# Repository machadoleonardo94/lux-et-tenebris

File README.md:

# Lux et Tenebris

**Lux et Tenebris** is an open-source ESP32-based LED controller development platform featuring custom PCB hardware, firmware, and support for addressable LEDs, RGB strips, and various lighting effects.

## Disclaimer

### Most of the readme.md present here was writen by Clanker, as a proof of concept for fast doccumentation generation. It may not contain the newest features, but it's good enough as a placeholder. Considering that it took 2 prompts and minor fixes, time that would've been used on this document was allocated elsewere more productive, like the main features.

But you know what? Using Clankers' template made the doccumentation much more enjoyable, and ended up with way more content than all of my previous projects combined, as after reading it I've managed to add tidbits that I wouldn't have written otherwise.

## Demo Video

https://github.com/user-attachments/assets/9bc4d82b-29f8-49ef-8373-876afc4fa7dd

### [Install firmware](install/)
A fresh, blank board needs nothing but a browser. Open the flasher in **Chrome or Edge on a
desktop**, plug the ESP32-C3 in over USB-C, click **Install** — no Python, no esptool, no USB-serial
driver, because the C3's USB is native.

**[⚡ Browser installer](install/)** · **[⬇ Release downloads](Firmware/lightpack-C3/releases/)** · **[How the installer works](install/README.md)**

- It explains itself when it cannot work (Firefox, Safari, mobile, or a `file://` copy) instead of
  showing a dead button, and links the command-line fallback.
- Works offline as well: serve this repository with `python -m http.server 8000` and open
  <http://localhost:8000/install/>.
- After flashing: join the `Lightpack-Devkit` hotspot, then use <http://lightpack.local>.

### [Hardware](Hardware/)
Custom PCB designs created in KiCad for the Lux et Tenebris devkit. Includes production-ready files for JLCPCB assembly.

**[📖 Hardware Documentation](Hardware/README.md)**

**Features:**
- ESP32-based design (4MB Flash)
- USB-C connectivity
- 4x WS2812B addressable LED channels
- 3x Open drain outputs + 1x controlled current output
- I2C expansion port for OLED display (SSD1306)
- Multiple expansion ports (Serial, I2C, GPIO)
- Production files ready for manufacturing

### [Firmware](Firmware/)
Arduino-based firmware with WiFi connectivity, OTA updates, and dynamic LED effects. Two
boards, two projects:

| Project | Board | Status | Install |
|---|---|---|---|
| **[lightpack-C3](Firmware/lightpack-C3/)** | Lux et Portabilis **V2** (ESP32-C3 SuperMini) | **Pre-release V0.4-pre** | **[⚡ Browser installer](install/)** · **[⬇ Downloads](Firmware/lightpack-C3/releases/V0.4-pre/)** |
| [lightpack](Firmware/lightpack/) | Lux et Tenebris **Devkit** (ESP32-WROOM) | V1.0 | Build from source |

**lightpack-C3 (Portabilis V2)** — current work:

- WiFi connectivity with captive portal configuration, 2 saved networks, offline (radio-off) mode
- Two OTA paths: ArduinoOTA and a **browser firmware upload** from the device page
- Single-channel WS2812B LED control with 5 modes (solid, flame, gyro fade, pulse whip, rainbow)
- MPU6050 accelerometer, impact detector, I²C bus scan, rail-voltage telemetry
- Battery latch power control, on-device menu, non-volatile storage for every setting
- 5 versioned preset slots with web import/export
- **[⚡ Browser installer](install/)**: Flash a blank board from Chrome/Edge — no tools, no drivers
- **[📖 Firmware Documentation](Firmware/lightpack-C3/README.md)** · **[📋 Release notes](Firmware/lightpack-C3/CHANGELOG.md)** · **[⬇ V0.4-pre binaries](Firmware/lightpack-C3/releases/V0.4-pre/)**

**lightpack (Devkit V1)** — **[📖 Firmware Documentation](Firmware/lightpack/README.md)**

- Multi-channel WS2812B LED control with effects
- OLED display integration
- Power management and deep sleep support
- User interface with button controls

##  Key Features

### Hardware Capabilities
- **4 Independent addressable LED Channels**: Control multiple WS2812B strips simultaneously
- **High-Current Outputs**: Open drain and constant current outputs for various LED types
- **Expandable Design**: JST-GH connectors for easy expansion
- **Compact Form Factor**: Optimized between integration into props and projects, and ease to build.

### Firmware Capabilities
- **Dynamic LED Effects**: Breathing, color cycling, chase effects, and custom patterns
- **WiFi Management**: Easy network configuration via captive portal
- **OTA Updates**: Update firmware wirelessly without USB connection
- **Display Integration**: Real-time status information on OLED
- **Power Efficient**: Deep sleep mode and WiFi toggle for battery applications
- **Customizable**: Modular code structure for easy modification

##  Use Cases

- **Cosplay Props**: Control LEDs in costumes, masks, and accessories
- **Art Installations**: Multi-channel LED art with dynamic effects
- **Home Automation**: WiFi-connected lighting control
- **Prototyping**: Development platform for LED-based projects
- **Educational**: Learn ESP32, LED control, and PCB design

## 📚 Documentation

- **[Hardware Documentation](Hardware/README.md)**: PCB design, assembly, and manufacturing
- **[Browser installer](install/)**: How to flash a fresh board, and how to run/host the flasher
- **[Portabilis V2 Firmware](Firmware/lightpack-C3/README.md)**: Download, flashing, controls, web API
- **[Portabilis V2 Release notes](Firmware/lightpack-C3/CHANGELOG.md)**: What shipped, upgrade notes, known issues
- **[Firmware Documentation](Firmware/lightpack/README.md)**: Devkit V1 setup, configuration, and API reference
- **Pinout Reference**: See the per-board firmware README for complete pin assignments
- **Manufacturing Files**: BOM, positions, and Gerbers in `Hardware/*/production/`

## 🧰 Technology Stack

### Hardware
- **PCB Design**: KiCad 9.0
- **Microcontroller**: ESP32-WROOM-32
- **Manufacturing**: JLCPCB-ready production files
- **Components**: Standard 0805 SMD parts for easy sourcing

### Firmware
- **Framework**: Arduino (PlatformIO)
- **Platform**: Espressif32
- **Language**: C++
- **Libraries**: Adafruit GFX, NeoPixel, WiFiManager, ArduinoOTA

## 💡 Getting Help

- **Hardware Issues**: See [Hardware README](Hardware/README.md)
- **Firmware Issues**: See [Firmware README](Firmware/lightpack/README.md)
- **Pin Configurations**: Check `Firmware/lightpack/src/shared/pinout.h`
- **GitHub Issues**: [Report bugs or request features](https://github.com/machadoleonardo94/lux-et-tenebris/issues)

##  Acknowledgments

Special thanks to:
- The ESP32 and Arduino communities
- Espressif 
- KiCad development team
- PlatformIO for the excellent development platform
- All contributors and users of this project

---

## License

This project is released under the **BSD Zero Clause License (0BSD)** — see [`LICENSE`](LICENSE).
Use it, modify it, sell it, strip my name off it, no conditions and no attribution required.

Two things that come with that:

- **Compiled firmware images link third-party libraries** whose licenses travel with the binary. The
  Arduino-ESP32 core (LGPL-2.1-or-later) and Adafruit NeoPixel (LGPL-3.0-or-later) are the ones with
  real terms: keep their notices, keep them under LGPL, and make sure recipients can reach the source
  to relink. Everything else is MIT/BSD/Apache. Full audit, per-library copyright lines and license
  texts in [`THIRD-PARTY-NOTICES.md`](THIRD-PARTY-NOTICES.md) and [`LICENSES/`](LICENSES/).
- **The KiCad symbol libraries** used by the schematics are CC-BY-SA-4.0 with a design exception, so
  using them imposes nothing on the boards. Their files are not redistributed here.

---

**Note**: This is an active development project. Hardware and firmware specifications may change. Always refer to the specific version documentation when building or programming your device.

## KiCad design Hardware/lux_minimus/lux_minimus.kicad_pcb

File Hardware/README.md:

# Lux et Tenebris Hardware

Hardware design files for the **Lux et Tenebris Devkit** - an ESP32-based LED controller development board with integrated OLED display, WS2812B LED channels, and multiple output configurations.

## Overview

The Lux et Tenebris hardware consists of custom PCB designs created in KiCad, providing a compact platform for controlling addressable LEDs, RGB strips, and other lighting applications. The board integrates power management and some I/O expansion ports.

## Hardware Versions

### lux-et-pcb (V1.0)
- Initial release
- Core ESP32 functionality
- DC 5521 connector for 5~24V external power
- USB-C charging port
- No integrated USB-Serial converter, requires an external one for burning firmware
- Optional 1S lithium charger and battery
- 4x WS2812B LED channels (5V from regulator or internal battery)
  - GPIOs 32, 33, 19 and 16 
- 3x Open drain outputs (for 12V RGB strips)
  - GPIOs 27, 26 and 25
- 1x Controlled current output (avoid pesky short-circuits frying your wires)
  - GPIO 13
- 2x expansion port with 3V3 power
  - Those can be set as other functions for external hardware
  - GPIOs 21 and 22 for I2C devices (display, gyro, be creative)
  - GPIOs 18 and 19 expansion port (control buttons)

### lux-et-pcb-V2
- Work in progress
- Changed the processor to ESP32-S3
- Added USB-C Serial interface (no more aditional hardware required for flashing)
- Added Sound output (be funky, no idea if it will work tho)
- Added microSD slot for SDMMC
- Modular schematic organization
- To do: 
  - Add I2S support (crispy sounds)
  - Add gyro support (so the board can do a PEW PEW noise when hit)
  - Remove added latch power-on switch 

## Features

### Core Specifications
- **Microcontroller**: ESP32 (4MB Flash)
- **Power Input**: USB-C connector or 5~24V 5521 connector (good old P4 with positive inside)
- **Display**: 0.96" SSD1306 OLED (128x64, I2C)
- **LED Channels**: 4x addressable WS2812B outputs
- **Power Outputs**: 3x open drain + 1x controlled current
- **Programming**: External USB-to-Serial (CP210x or CH340) or OTA
- **Expansion Ports**: Serial, I2C, GPIOs

### Pinout

#### WS2812B LED Channels
| Channel   | GPIO Pin | Default Use              |
|-----------|----------|--------------------------|
| Channel 0 | GPIO 32  | Onboard LED ring (6 LEDs) |
| Channel 1 | GPIO 33  | External connector        |
| Channel 2 | GPIO 19  | External connector        |
| Channel 3 | GPIO 16  | External connector        |

#### Expansion Ports
| Port  | Connector | Pins                     | Function             |
|-------|-----------|--------------------------|----------------------|
| PORT1 | JST-GH 4P | GND, TX0, RX0, 5V        | Serial/Power         |
| PORT2 | JST-GH 4P | GND, GPIO18, GPIO17, 3V3 | Button/GPIO Inputs   |
| PORT3 | JST-GH 4P | GND, SCL, SDA, 3V3       | I2C Display/Sensors  |

#### Power Outputs
- **CC Output**: GPIO 13 - Constant current output (~700mA) for high-power LEDs
- **Open Drain**: GPIO 27, 26, 25 - For RGB strips or high-current switching

### Key Components
- ESP32-WROOM-32 module
- Programming and reset push buttons
- USB-C connector (GT-USB-7101A, optional)
- JST-GH 1.25mm connectors (4-pin)
- Good quality 220uF 25V 6.3x7.7mm (bad quality ones tend to heat up)
- SSD1306 0.96" OLED display (optional)
- Onboard WS2812B LED ring (optional)
- Onboard 1S lithium battery and charger (optional)
- Onboard LED for 3V3 and battery charging status (optional)
- AO340X N-MOS SOT23 transistors or equivalent that can handle at least 1A for each open collector strip channel

Full list should be on the BoM files, with codes for used component on LCSC

## PCB Design Files

Each hardware version includes:
- **`.kicad_pcb`** - PCB layout file
- **`.kicad_sch`** - Schematic file
- **`.kicad_pro`** - Project configuration
- **`.step`** - 3D model for mechanical integration
- **`production/`** - Manufacturing files (BOM, positions, netlist) for JLCPCB

## Manufacturing

### JLCPCB Assembly Service

The design is optimized for JLCPCB's PCB assembly service:

1. **PCB Fabrication + Assembly**: ~$130 for 5 boards (assembled)
2. **Files Included**:
   - `bom.csv` - Bill of Materials
   - `positions.csv` - Component placement data
   - `netlist.ipc` - Connectivity information
   - `designators.csv` - Component reference designators

### DIY Assembly

For self-assembly:
- **Cost**: $8-15 per board (components only)
- **Recommended**: Solder stencil (~$7) for SMD components, and a reflow hotbed at 250ºC for melting solder paste
- **Skills**: Intermediate soldering (fine-pitch SMD)
- **Time**: ~1-3 hours per board.  

### Component Sourcing

Most components are standard and available from:
- JLCPCB parts library (for assembly service)
- LCSC
- Mouser
- DigiKey
- Aliexpress

Special components:
- **USB-C connector**: GT-USB-7101A (included in design files)
Getting the correct USB-C connector with dozen of options is very hard if sourcing from Aliexpress.
If you do not require USB-C charging, this component can be avoided.

## Getting Started

### Prerequisites

1. **KiCad 8.0 or later** - [Download here](https://www.kicad.org/download/)
2. **3D Models** - Included `.step` files for mechanical clearance verification
3. **Symbol Library** - Custom `USB_C-8p.kicad_sym` included in project

### Generating Manufacturing Files

1. Open the PCB file in KiCad
2. Add the JLCPCB plugin from the Plugin and Content Manager
3. **Tools → External plugins → Fabrication toolkit**
4. Files should be generated on the production folder automagically 

## Assembly Instructions

### Hardware Assembly

0. **Read the issues and notes before assembly!**

1. **Solder SMD Components** (if self-assembling):
   - Use solder paste and stencil
   - Place components with tweezers
   - Reflow with hot air or reflow oven

2. **Through-hole Components**:
   - Cable wires for LED strips, or 2.54 3P terminal block
     - It's advised to use in-line connectors for power output, like the JST-3P
   - DC 5521 connector
   - XH-2.54 2P for battery (no one is stoping you from soldering the battery wires directly, but please try to act civilized (I did that, no judgement))

### Power-Up Checklist

- [ ] Visually inspect all solder joints
- [ ] Check for shorts between power and ground
- [ ] Power the board (no LEDs connected yet)
- [ ] Verify 3.3V rail
- [ ] Verify 5V rail
- [ ] Test USB-to-Serial communication
- [ ] Upload test firmware
- [ ] Watch the white circle blink
- [ ] Configure your WiFi SSID and password on the hotspot page
- [ ] If connected to the WiFi, blue breathing effect on onboard LEDs
- [ ] If !connected to the WiFi, color changing running pixel on onboard LEDs

## Integration with Firmware

The hardware is designed to work with the [Lightpack Firmware](../Firmware/lightpack/). 

**Pin configurations must match** between hardware and firmware - see `Firmware/lightpack/src/shared/pinout.h` for current assignments.

## Connector Wiring

### PORT1 (Serial/Power) - JST-GH 4P
```
Pin 1: GND
Pin 2: ESP32 TX0 (GPIO 1)
Pin 3: ESP32 RX0 (GPIO 3)
Pin 4: 5V (Power In)
```

### PORT2 (GPIO) - JST-GH 4P
```
Pin 1: GND
Pin 2: GPIO 18 (Button A)
Pin 3: GPIO 17 (Button B)
Pin 4: 3V3 Out
```

### PORT3 (I2C) - JST-GH 4P
```
Pin 1: GND
Pin 2: SCL (GPIO 22)
Pin 3: SDA (GPIO 21)
Pin 4: 3V3 Out
```

## Design Considerations

### Power Management
- The switched DC-DC regulator 5V output is limited to 900mA by the 33uH inductor
- The battery charger is set to 500mA
- When powering from DC 5521 connector, avoid drawing more than 300mA from the 5V LEDs to avoid a processor brownout. The processor current draw can peak about 200mA during WiFi usage.
- There's a 500mA resetable fuse for the 3V3 regulator that shunts the current to a safe 200mA in case of a short circuit, but it's response is slow.

## Known Issues & Notes

### V1.0
- Initial production version
- Reverse voltage P-MOS protection is wired wrong (swapped gate and source terminals)
- Board will not receive external nor battery power because of this
- Swap the SOT-223 transistor for an SS14 schottky diode

- Wrong footprints for R8 and R10 0R22 resistors. Used 2010, should have been 1206
- Charge status and 3V3 LEDs too bright, put 5.1kR series resistor instead of 2.2kR or remove them altogether

### Tools
- [KiCad](https://www.kicad.org/) - PCB design software
  - JLCPCB Fabrication toolkit plugin
- [JLCPCB](https://jlcpcb.com/) - PCB manufacturing
- Autodesk Fusion360 - Case moddeling

## Cost Breakdown

### JLCPCB Assembly (5 boards)
- PCB Fabrication: ~$2
- Component Costs: ~$45
- Assembly Service: ~$85
- **Total**: ~$130 + shipping

### Self-Assembly (per board)
- PCB only: ~$3 (in batch of 5)
- Components: $8-15
- **Total**: ~$10-18 per board

**Note**: Always verify pin configurations match between hardware version and firmware before uploading code. Check the schematic and `pinout.h` for current assignments.

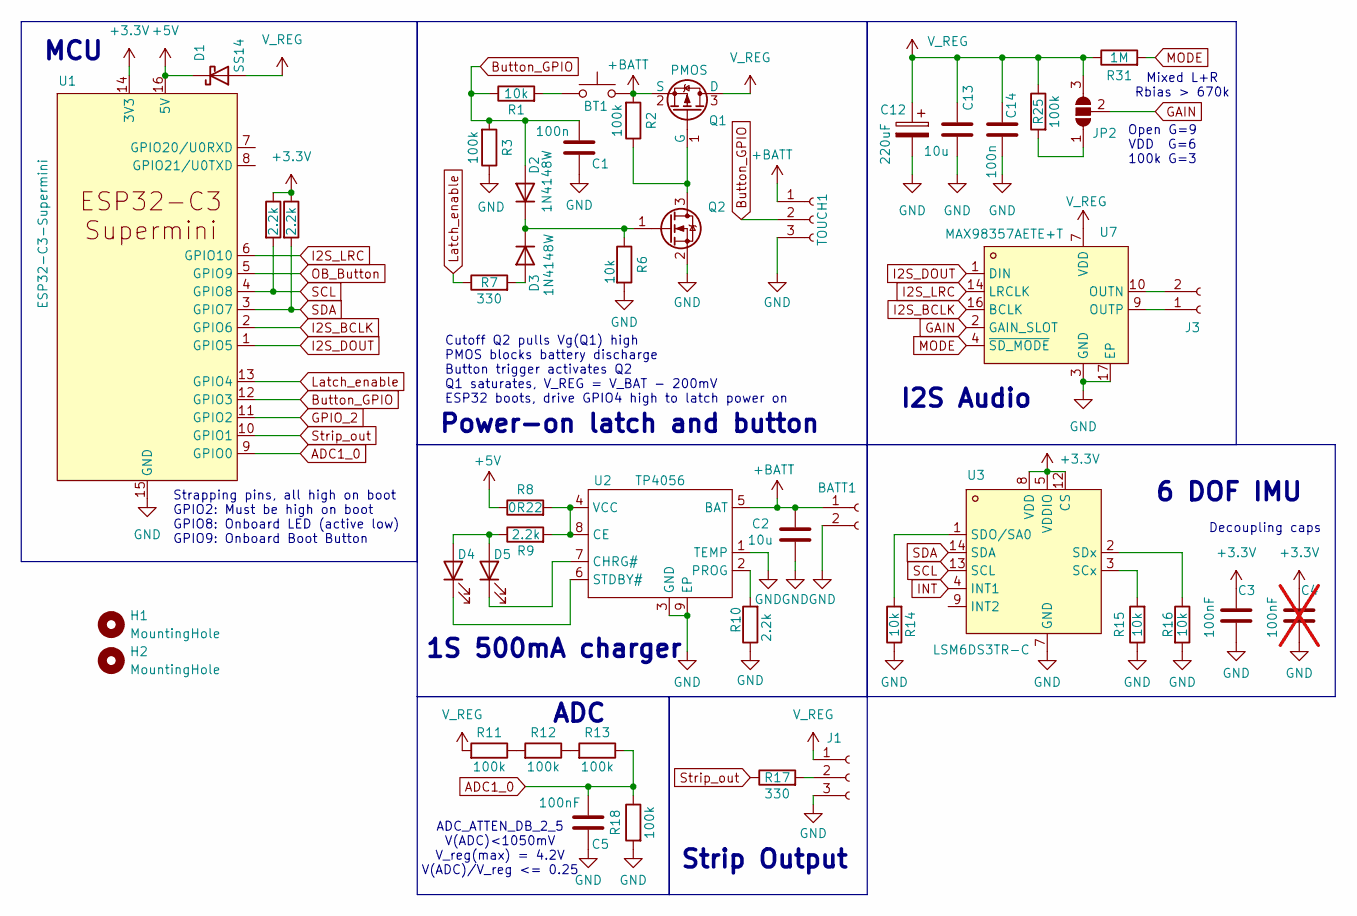
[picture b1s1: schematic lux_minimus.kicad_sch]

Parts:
BATT1: Conn_01x02_Socket; Molex_KK-254_AE-6410-02A_1x02_P2.54mm_Vertical; LCSC C49023803
BT1: SW_Push; SW_SPST_PTS647_Sx38; LCSC C2888502
C1, C14: 100n; C_0805_2012Metric_Pad1.18x1.45mm_HandSolder; LCSC C49678
C2: 10u; C_0805_2012Metric; LCSC C15850
C3, C5: 100nF; C_0805_2012Metric; Mfr. Part Number CC0805KRX7R9BB104; LCSC C49678
C4: 100nF; C_0805_2012Metric; Mfr. Part Number CC0805KRX7R9BB104; LCSC C49678; not fitted
C12: 220uF; Cap_polymer; LCSC C2162971
C13: 10u; C_0805_2012Metric_Pad1.18x1.45mm_HandSolder; LCSC C162422
D1: SS14; D_SMA; LCSC C2480
D2, D3: 1N4148W; D_SOD-123; LCSC C83528
D4: LED_BLUE; LED_0805_2012Metric_Pad1.15x1.40mm_HandSolder; LCSC C965817
D5: LED_RED; LED_0805_2012Metric_Pad1.15x1.40mm_HandSolder; LCSC C84256
H1, H2: MountingHole; MountingHole_3.2mm_M3
J1: Conn_01x03_Socket; TerminalBlock_Xinya_XY308-2.54-3P_1x03_P2.54mm_Horizontal
J3: Conn_01x02_Socket; Molex_PicoBlade_53261-0271_1x02-1MP_P1.25mm_Horizontal; LCSC C7433468
JP2: SolderJumper_3_Open; SolderJumper-3_P1.3mm_Open_RoundedPad1.0x1.5mm
Q1: PMOS; SOT-23_Handsoldering; LCSC C42456992
Q2: 2N7002K; SOT-23; LCSC C65189
R1, R6, R14, R15, R16: 10k; R_0805_2012Metric_Pad1.20x1.40mm_HandSolder; LCSC C17414
R2, R3, R25: 100k; R_0805_2012Metric_Pad1.20x1.40mm_HandSolder; LCSC C149504
R4, R5, R9, R10: 2.2k; R_0805_2012Metric; LCSC C17520
R7: 330; R_0805_2012Metric_Pad1.20x1.40mm_HandSolder; LCSC C17630
R8: 0R22; R_1206_3216Metric_Pad1.30x1.75mm_HandSolder; LCSC C2683384
R11, R12, R13, R18: 100k; R_0805_2012Metric; LCSC C149504
R17: 330; R_0805_2012Metric; LCSC C17630
R31: 1M; R_0805_2012Metric_Pad1.20x1.40mm_HandSolder; LCSC 1
TOUCH1: Conn_01x03_Socket; PinHeader_1x03_P2.54mm_Vertical
U1: ESP32-C3-Supermini
U2: TP4056; ESOP-8_L4.9-W3.9-P1.27-LS6.0-BL-EP; LCSC Part Name 1A锂电池充电IC
U3: LSM6DS3TR-C; LGA-14_L3.0-W2.5-P0.50-TL; MPN LSM6DS3TR-C; LCSC Part C967633
U7: MAX98357AETE+T; TQFN-16_L3.0-W3.0-P0.50-BL-EP1.5; MPN MAX98357AETE+T; LCSC Part C910544

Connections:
+3.3V: C3.2, C4.2, R4.1, R5.1, U1.14 (3V3), U3.5 (VDDIO), U3.8 (VDD), U3.12 (CS)
+5V: D1.1 (K), R8.1, U1.16 (5V)
+BATT: BATT1.1, BT1.1, C2.1, Q1.2 (S), R2.2, TOUCH1.1, U2.5 (BAT)
ADC1_0: C5.2, R13.1, R18.1, U1.9 (GPIO0)
Button_GPIO: C1.2, D2.2 (A), R1.1, R3.2, TOUCH1.2, U1.12 (GPIO3)
GAIN: JP2.2 (C), U7.2 (GAIN_SLOT)
GND: BATT1.2, C1.1, C2.2, C3.1, C4.1, C5.1, C12.2, C13.2, C14.1, J1.3, Q2.2 (S), R3.1, R6.2, R10.1, R14.1, R15.1, R16.2, R18.2, TOUCH1.3, U1.15 (GND), U2.1 (TEMP), U2.3 (GND), U2.9 (EP), U3.6 (GND), U3.7 (GND), U7.3 (GND), U7.11 (GND), U7.15 (GND), U7.17 (EP)
GPIO_2: U1.11 (GPIO2)
I2S_BCLK: U1.2 (GPIO6), U7.16 (BCLK)
I2S_DOUT: U1.1 (GPIO5), U7.1 (DIN)
I2S_LRC: U1.6 (GPIO10), U7.14 (LRCLK)
INT: U3.4 (INT1)
Latch_enable: R7.1, U1.13 (GPIO4)
MODE: R31.2, U7.4 (~SD_MODE)
unnamed: BT1.2, R1.2
unnamed: D2.1 (K), D3.1 (K), Q2.1 (G), R6.1
unnamed: D3.2 (A), R7.2
unnamed: D4.2 (A), D5.2 (A), R9.1
unnamed: D4.1 (K), U2.6 (STDBY#)
unnamed: D5.1 (K), U2.7 (CHRG#)
unnamed: J1.2, R17.2
unnamed: J3.1, U7.9 (OUTP)
unnamed: J3.2, U7.10 (OUTN)
unnamed: JP2.1 (A), R25.2
unnamed: Q1.1 (G), Q2.3 (D), R2.1
unnamed: R11.1, R12.2
unnamed: R12.1, R13.2
unnamed: R8.2, R9.2, U2.4 (VCC), U2.8 (CE)
unnamed: R10.2, U2.2 (PROG)
unnamed: R15.2, U3.3 (SCx)
unnamed: R14.2, U3.1 (SDO/SA0)
unnamed: R16.1, U3.2 (SDx)
OB_Button: U1.5 (GPIO9)
SCL: R4.2, U1.4 (GPIO8), U3.13 (SCL)
SDA: R5.2, U1.3 (GPIO7), U3.14 (SDA)
Strip_out: R17.1, U1.10 (GPIO1)
V_REG: C12.1, C13.1, C14.2, D1.2 (A), J1.1, JP2.3 (B), Q1.3 (D), R11.2, R25.1, R31.1, U7.7 (VDD), U7.8 (VDD)

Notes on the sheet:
Strip Output
Cutoff Q2 pulls Vg(Q1) high PMOS blocks battery discharge Button trigger activates Q2 Q1 saturates, V_REG = V_BAT - 200mV ESP32 boots, drive GPIO4 high to latch power on
ADC_ATTEN_DB_2_5 V(ADC)<1050mV V_reg(max) = 4.2V V(ADC)/V_reg <= 0.25
Mixed L+R Rbias > 670k
MCU
ADC
Strapping pins, all high on boot GPIO2: Must be high on boot GPIO8: Onboard LED (active low) GPIO9: Onboard Boot Button
1S 500mA charger
Decoupling caps
6 DOF IMU
Open G=9 VDD G=6 100k G=3
I2S Audio
Power-on latch and button

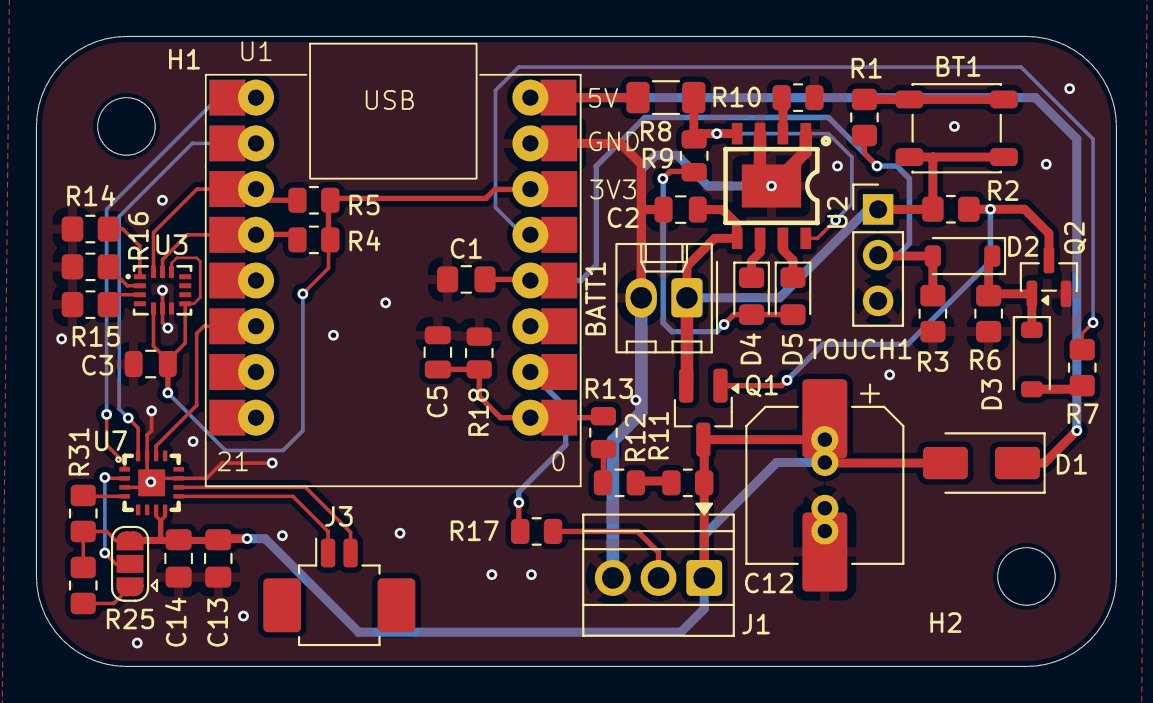
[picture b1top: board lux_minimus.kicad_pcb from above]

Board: 2 copper layers, 60.0 x 35.0 mm, 46 parts (0 on the bottom side), 34 nets.

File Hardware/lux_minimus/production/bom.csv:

Designator,Footprint,Quantity,Value,LCSC Part #
BT1,SW_SPST_PTS647_Sx38,1,SW_Push,C2888502
"C1, C14",0805,2,100n,C49678
C12,Cap_polymer,1,220uF,C2162971
C13,0805,1,10u,C162422
C2,0805,1,10u,C15850
"C3, C5",0805,2,100nF,C49678
D1,D_SMA,1,SS14,C2480
"D2, D3",D_SOD-123,2,1N4148W,C83528
D4,0805,1,LED_BLUE,C965817
D5,0805,1,LED_RED,C84256
J1,TerminalBlock_Xinya_XY308-2.54-3P_1x03_P2.54mm_Horizontal,1,Conn_01x03_Socket,
J3,Molex_PicoBlade_53261-0271_1x02-1MP_P1.25mm_Horizontal,1,Conn_01x02_Socket,C7433468
Q1,SOT-23_Handsoldering,1,PMOS,C42456992
Q2,SOT-23,1,2N7002K,C65189
"R1, R14, R15, R16, R6",0805,5,10k,C17414
"R10, R4, R5, R9",0805,4,2.2k,C17520
"R11, R12, R13, R18, R2, R25, R3",0805,7,100k,C149504
"R17, R7",0805,2,330,C17630
R31,0805,1,1M,1
R8,1206,1,0R22,C2683384
TOUCH1,PinHeader_1x03_P2.54mm_Vertical,1,Conn_01x03_Socket,
U1,ESP32-C3-Supermini,1,ESP32-C3-Supermini,
U2,ESOP-8_L4.9-W3.9-P1.27-LS6.0-BL-EP,1,TP4056,C382139
U3,LGA-14_L3.0-W2.5-P0.50-TL,1,LSM6DS3TR-C,C967633
U7,TQFN-16_L3.0-W3.0-P0.50-BL-EP1.5,1,MAX98357AETE+T,C910544

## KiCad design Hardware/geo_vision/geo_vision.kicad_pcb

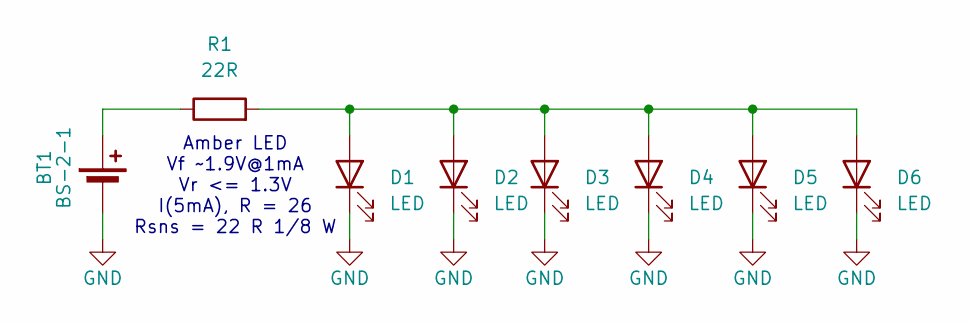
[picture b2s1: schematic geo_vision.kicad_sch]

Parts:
BT1: BS-2-1; BatteryHolder_MYOUNG_BS-07-A1BJ001_CR2032; Mfr. Part Number BS-2-1; LCSC C70376
D1, D2, D3, D4, D5, D6: LED; LED_0805_2012Metric
R1: 22R; R_0805_2012Metric_Pad1.20x1.40mm_HandSolder

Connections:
GND: BT1.2 (-), D1.1 (K), D2.1 (K), D3.1 (K), D4.1 (K), D5.1 (K), D6.1 (K)
unnamed: BT1.1 (+), R1.1
unnamed: D1.2 (A), D2.2 (A), D3.2 (A), D4.2 (A), D5.2 (A), D6.2 (A), R1.2

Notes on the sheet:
Amber LED Vf ~1.9V@1mA Vr <= 1.3V I(5mA), R = 26 Rsns = 22 R 1/8 W

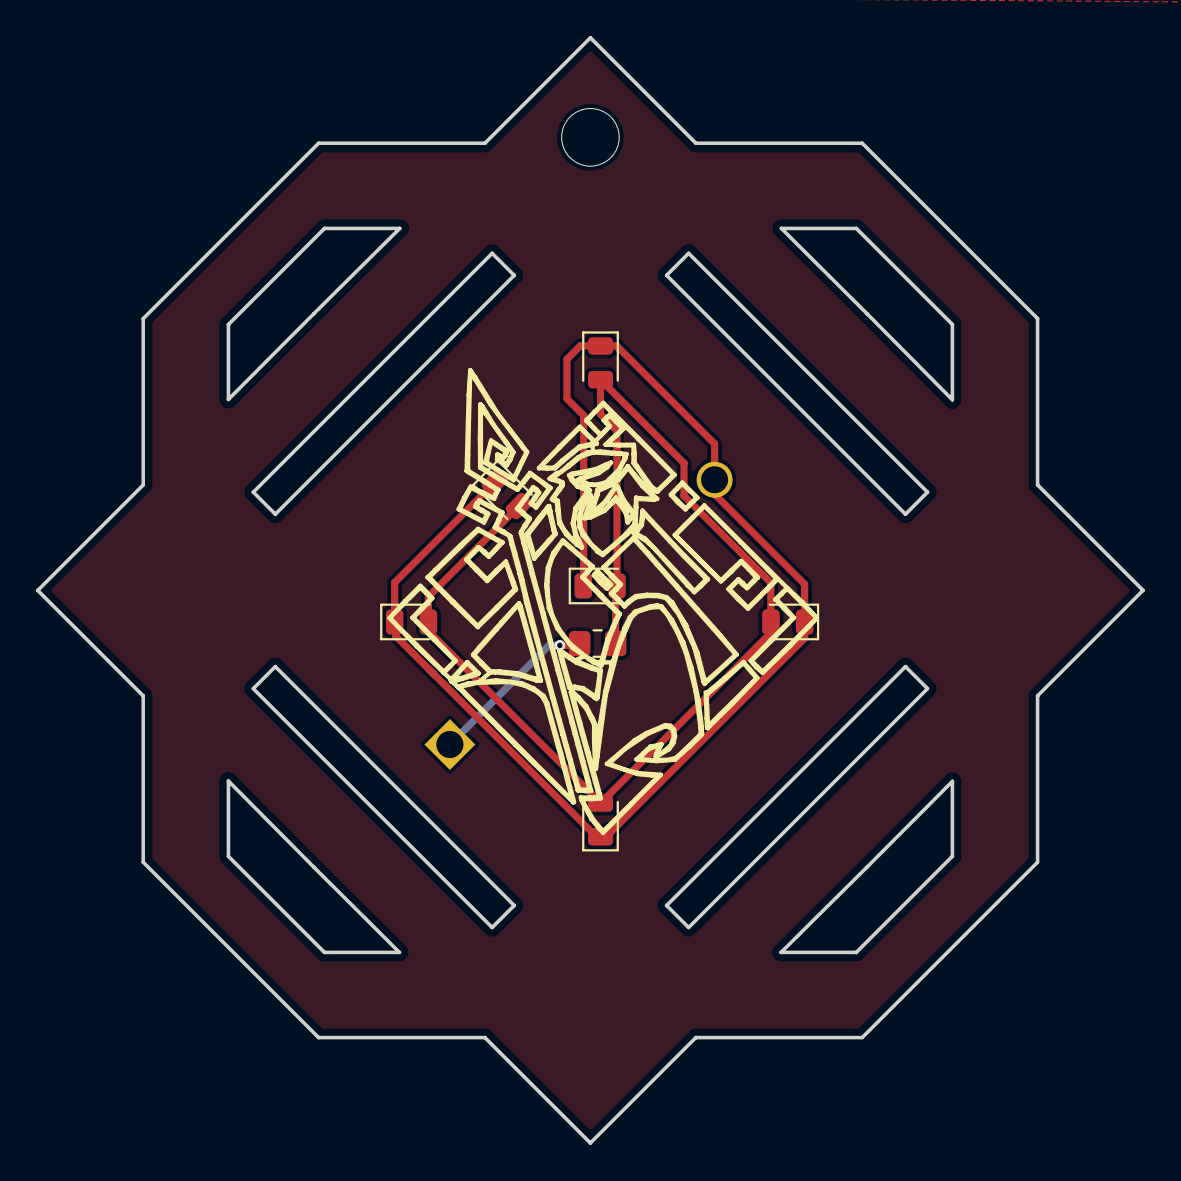
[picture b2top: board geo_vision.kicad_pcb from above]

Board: 2 copper layers, 61.4 x 61.4 mm, 8 parts (1 on the bottom side), 3 nets.

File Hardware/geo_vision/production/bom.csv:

Designator,Footprint,Quantity,Value,LCSC Part #
BT1,BatteryHolder_MYOUNG_BS-07-A1BJ001_CR2032,1,BS-2-1,C70376
"D1, D2, D3, D4, D5, D6",0805,6,LED,
R1,0805,1,22R,

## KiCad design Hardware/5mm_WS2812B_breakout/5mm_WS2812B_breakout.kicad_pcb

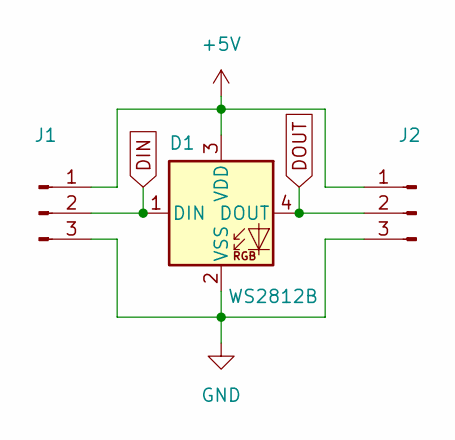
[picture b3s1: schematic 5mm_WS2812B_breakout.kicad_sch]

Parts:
D1: WS2812B; WS2812B_PTH_staggered
J1, J2: Conn_01x03_Pin; PinHeader_1x03_P2.54mm_Vertical

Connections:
+5V: D1.3 (VDD), J1.1, J2.1
DIN: D1.1 (DIN), J1.2
DOUT: D1.4 (DOUT), J2.2
GND: D1.2 (VSS), J1.3, J2.3

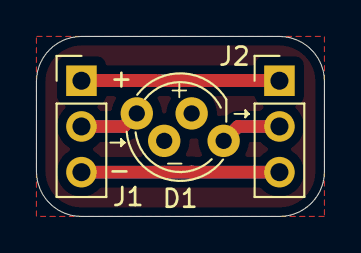
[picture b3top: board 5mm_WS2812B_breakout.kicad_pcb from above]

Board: 2 copper layers, 16.0 x 10.0 mm, 3 parts (0 on the bottom side), 4 nets.

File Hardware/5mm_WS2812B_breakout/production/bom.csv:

Designator,Footprint,Quantity,Value,LCSC Part #
D1,WS2812B_PTH_staggered,1,WS2812B,
"J1, J2",PinHeader_1x03_P2.54mm_Vertical,2,Conn_01x03_Pin,

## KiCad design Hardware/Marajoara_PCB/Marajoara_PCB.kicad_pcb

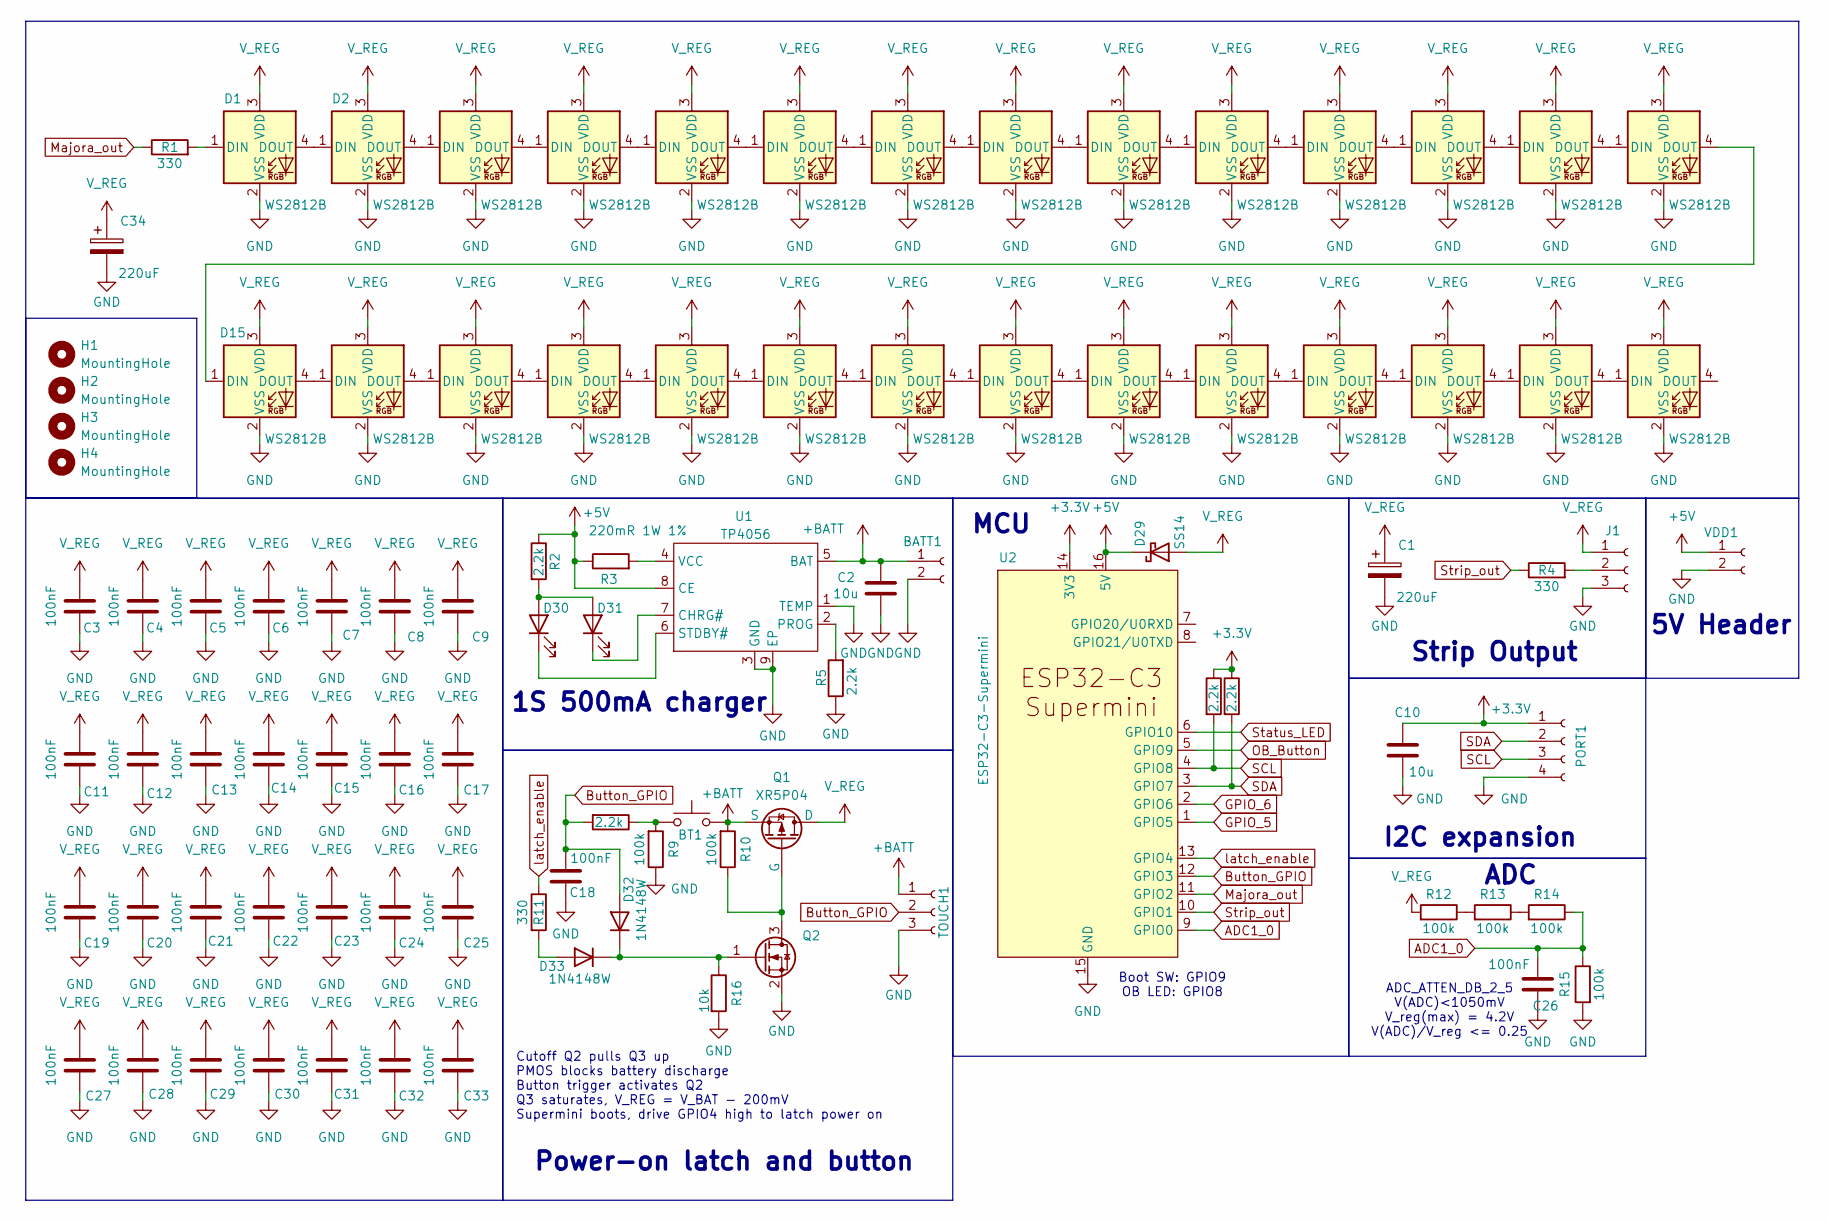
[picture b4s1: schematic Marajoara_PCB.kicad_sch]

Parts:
BATT1: Conn_01x02_Socket; Molex_KK-254_AE-6410-02A_1x02_P2.54mm_Vertical; LCSC C49023803
BT1: SW_Push; SW_SPST_PTS647_Sx38; LCSC C455246
C1, C34: 220uF; CP_Elec_6.3x7.7; Mfr. Part Number 35TKV220M8X10.5; LCSC C25170691
C2, C10: 10u; C_0805_2012Metric; LCSC C15850
C3, C4, C5, C6, C7, C8, C9, C11, C12, C13, C14, C15, C16, C17, C18, C19, C20, C21, C22, C23, C24, C25, C26, C27, C28, C29, C30, C31, C32, C33: 100nF; C_0805_2012Metric; Mfr. Part Number CC0805KRX7R9BB104; LCSC C49678
D1, D2, D3, D4, D5, D6, D7, D8, D9, D10, D11, D12, D13, D14, D15, D16, D17, D18, D19, D20, D21, D22, D23, D24, D25, D26, D27, D28: WS2812B; WS2812B_PTH_staggered
D29: SS14; D_SMA; LCSC C2480
D30: LED_BLUE; LED_0805_2012Metric_Pad1.15x1.40mm_HandSolder; LCSC C965817
D31: LED_RED; LED_0805_2012Metric_Pad1.15x1.40mm_HandSolder; LCSC C84256
D32, D33: 1N4148W; D_SOD-123; Mfr. Part Number 1N4148W-7-F; LCSC C83528
H1, H2, H3, H4: MountingHole; MountingHole_3.2mm_M3
J1: Conn_01x03_Socket; TerminalBlock_Xinya_XY308-2.54-3P_1x03_P2.54mm_Horizontal
PORT1: Conn_01x04_Socket; Hirose_DF13C_CL535-0404-8-51_1x04-1MP_P1.25mm_Vertical; LCSC C7433470
Q1: XR5P04; SOT-23_Handsoldering; LCSC C42456992
Q2: 2N7002K; SOT-23; LCSC C65189
R1, R4, R11: 330; R_0805_2012Metric; LCSC C17630
R2, R5, R6, R7, R8: 2.2k; R_0805_2012Metric; LCSC C17520
R3: 220mR 1W 1%; R_1206_3216Metric_Pad1.30x1.75mm_HandSolder; Mfr. Part Number RLH12FTCR220; LCSC C2683384
R9, R10, R12, R13, R14, R15: 100k; R_0805_2012Metric; LCSC C149504
R16: 10k; R_0805_2012Metric; LCSC C17414
TOUCH1: Conn_01x03_Socket; PinHeader_1x03_P2.54mm_Vertical
U1: TP4056; ESOP-8_L4.9-W3.9-P1.27-LS6.0-BL-EP; LCSC Part Name 1A锂电池充电IC
U2: ESP32-C3-Supermini
VDD1: Conn_01x02_Socket; Molex_KK-254_AE-6410-02A_1x02_P2.54mm_Vertical; LCSC C49023803

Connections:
+3.3V: C10.1, PORT1.1, R6.1, R7.1, U2.14 (3V3)
+5V: D29.1 (K), R2.1, R3.1, U1.8 (CE), U2.16 (5V), VDD1.1
+BATT: BATT1.1, BT1.1, C2.1, Q1.2 (S), R10.2, TOUCH1.1, U1.5 (BAT)
ADC1_0: C26.2, R14.1, R15.1, U2.9 (GPIO0)
Button_GPIO: C18.2, D32.2 (A), R8.2, TOUCH1.2, U2.12 (GPIO3)
GND: BATT1.2, C1.2, C2.2, C3.1, C4.1, C5.1, C6.1, C7.1, C8.1, C9.1, C10.2, C11.1, C12.1, C13.1, C14.1, C15.1, C16.1, C17.1, C18.1, C19.1, C20.1, C21.1, C22.1, C23.1, C24.1, C25.1, C26.1, C27.1, C28.1, C29.1, C30.1, C31.1, C32.1, C33.1, C34.2, D1.2 (VSS), D2.2 (VSS), D3.2 (VSS), D4.2 (VSS), D5.2 (VSS), D6.2 (VSS), D7.2 (VSS), D8.2 (VSS), D9.2 (VSS), D10.2 (VSS), D11.2 (VSS), D12.2 (VSS), D13.2 (VSS), D14.2 (VSS), D15.2 (VSS), D16.2 (VSS), D17.2 (VSS), D18.2 (VSS), D19.2 (VSS), D20.2 (VSS), D21.2 (VSS), D22.2 (VSS), D23.2 (VSS), D24.2 (VSS), D25.2 (VSS), D26.2 (VSS), D27.2 (VSS), D28.2 (VSS), J1.3, PORT1.4, Q2.2 (S), R5.1, R9.1, R15.2, R16.2, TOUCH1.3, U1.1 (TEMP), U1.3 (GND), U1.9 (EP), U2.15 (GND), VDD1.2
GPIO_5: U2.1 (GPIO5)
GPIO_6: U2.2 (GPIO6)
Majora_out: R1.1, U2.11 (GPIO2)
unnamed: BT1.2, R8.1, R9.2
unnamed: D1.1 (DIN), R1.2
unnamed: D1.4 (DOUT), D2.1 (DIN)
unnamed: D2.4 (DOUT), D3.1 (DIN)
unnamed: D3.4 (DOUT), D4.1 (DIN)
unnamed: D4.4 (DOUT), D5.1 (DIN)
unnamed: D5.4 (DOUT), D6.1 (DIN)
unnamed: D6.4 (DOUT), D7.1 (DIN)
unnamed: D7.4 (DOUT), D8.1 (DIN)
unnamed: D8.4 (DOUT), D9.1 (DIN)
unnamed: D9.4 (DOUT), D10.1 (DIN)
unnamed: D10.4 (DOUT), D11.1 (DIN)
unnamed: D11.4 (DOUT), D12.1 (DIN)
unnamed: D12.4 (DOUT), D13.1 (DIN)
unnamed: D13.4 (DOUT), D14.1 (DIN)
unnamed: D14.4 (DOUT), D15.1 (DIN)
unnamed: D15.4 (DOUT), D16.1 (DIN)
unnamed: D16.4 (DOUT), D17.1 (DIN)
unnamed: D17.4 (DOUT), D18.1 (DIN)
unnamed: D18.4 (DOUT), D19.1 (DIN)
unnamed: D19.4 (DOUT), D20.1 (DIN)
unnamed: D20.4 (DOUT), D21.1 (DIN)
unnamed: D21.4 (DOUT), D22.1 (DIN)
unnamed: D22.4 (DOUT), D23.1 (DIN)
unnamed: D23.4 (DOUT), D24.1 (DIN)
unnamed: D24.4 (DOUT), D25.1 (DIN)
unnamed: D25.4 (DOUT), D26.1 (DIN)
unnamed: D26.4 (DOUT), D27.1 (DIN)
unnamed: D27.4 (DOUT), D28.1 (DIN)
unnamed: D30.2 (A), D31.2 (A), R2.2
unnamed: D30.1 (K), U1.6 (STDBY#)
unnamed: D31.1 (K), U1.7 (CHRG#)
unnamed: D32.1 (K), D33.1 (K), Q2.1 (G), R16.1
unnamed: D33.2 (A), R11.2
unnamed: J1.2, R4.2
unnamed: Q1.1 (G), Q2.3 (D), R10.1
unnamed: R12.1, R13.2
unnamed: R13.1, R14.2
unnamed: R5.2, U1.2 (PROG)
unnamed: R3.2, U1.4 (VCC)
OB_Button: U2.5 (GPIO9)
SCL: PORT1.3, R6.2, U2.4 (GPIO8)
SDA: PORT1.2, R7.2, U2.3 (GPIO7)
Status_LED: U2.6 (GPIO10)
Strip_out: R4.1, U2.10 (GPIO1)
V_REG: C1.1, C3.2, C4.2, C5.2, C6.2, C7.2, C8.2, C9.2, C11.2, C12.2, C13.2, C14.2, C15.2, C16.2, C17.2, C19.2, C20.2, C21.2, C22.2, C23.2, C24.2, C25.2, C27.2, C28.2, C29.2, C30.2, C31.2, C32.2, C33.2, C34.1, D1.3 (VDD), D2.3 (VDD), D3.3 (VDD), D4.3 (VDD), D5.3 (VDD), D6.3 (VDD), D7.3 (VDD), D8.3 (VDD), D9.3 (VDD), D10.3 (VDD), D11.3 (VDD), D12.3 (VDD), D13.3 (VDD), D14.3 (VDD), D15.3 (VDD), D16.3 (VDD), D17.3 (VDD), D18.3 (VDD), D19.3 (VDD), D20.3 (VDD), D21.3 (VDD), D22.3 (VDD), D23.3 (VDD), D24.3 (VDD), D25.3 (VDD), D26.3 (VDD), D27.3 (VDD), D28.3 (VDD), D29.2 (A), J1.1, Q1.3 (D), R12.2
latch_enable: R11.1, U2.13 (GPIO4)

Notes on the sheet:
Power-on latch and button
1S 500mA charger
ADC_ATTEN_DB_2_5 V(ADC)<1050mV V_reg(max) = 4.2V V(ADC)/V_reg <= 0.25
Cutoff Q2 pulls Q3 up PMOS blocks battery discharge Button trigger activates Q2 Q3 saturates, V_REG = V_BAT - 200mV Supermini boots, drive GPIO4 high to latch power on
Boot SW: GPIO9 OB LED: GPIO8
Strip Output
MCU
ADC
I2C expansion
5V Header

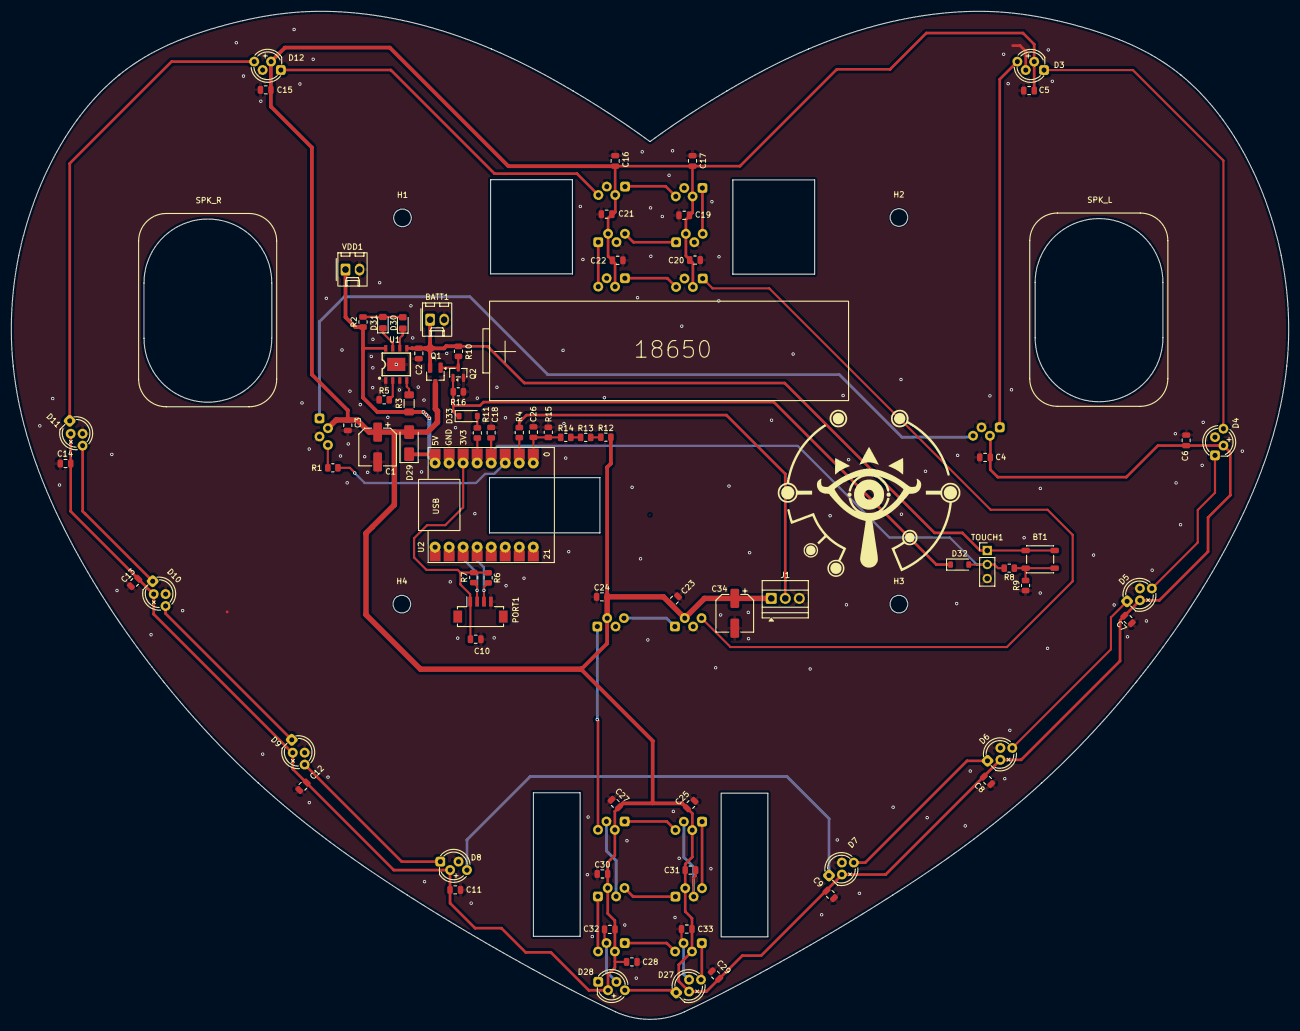
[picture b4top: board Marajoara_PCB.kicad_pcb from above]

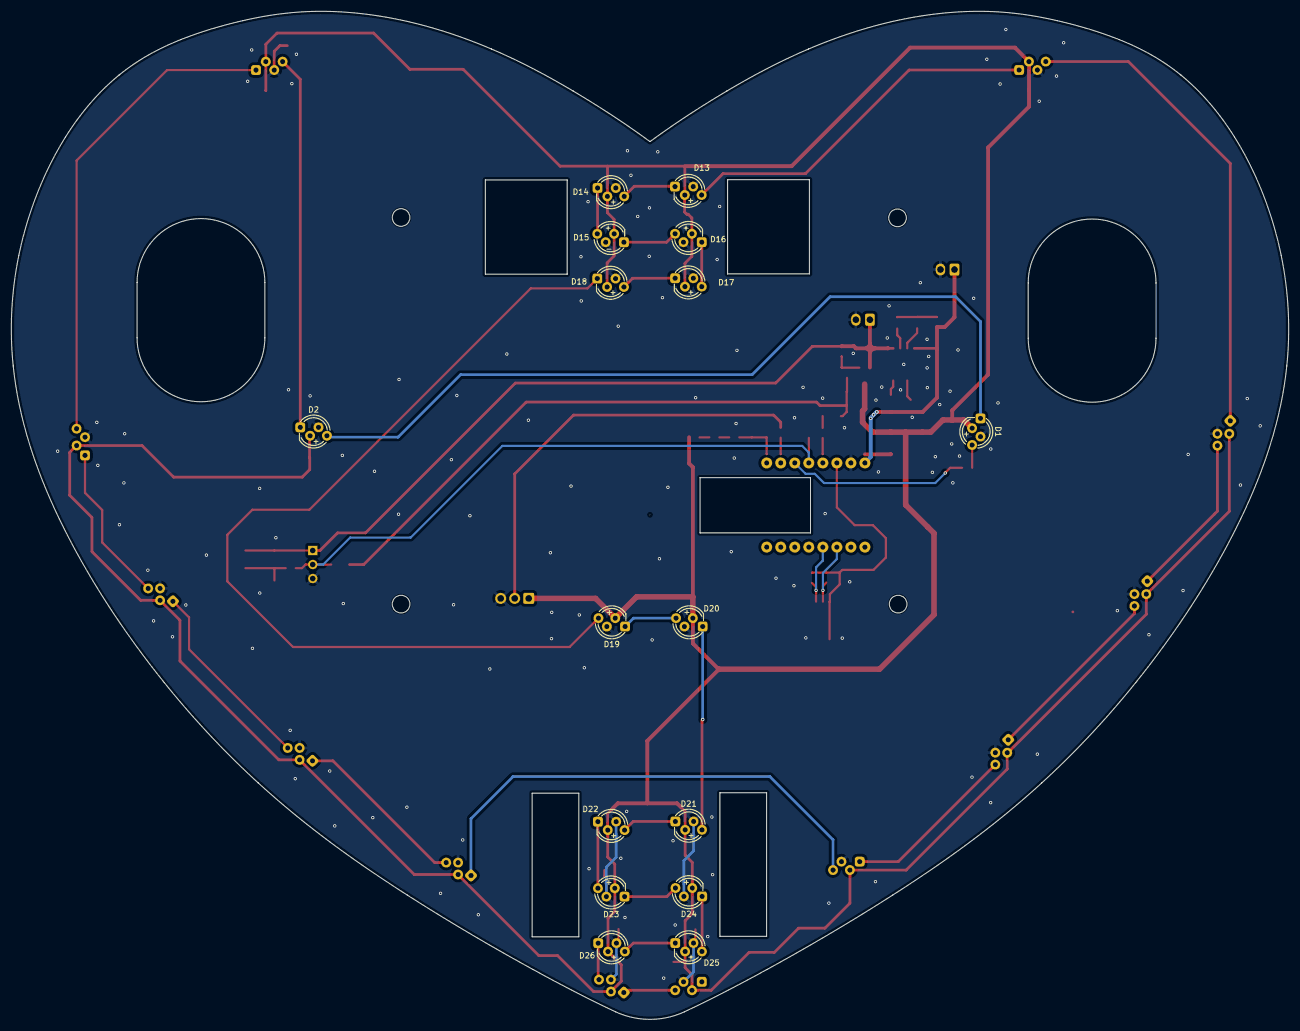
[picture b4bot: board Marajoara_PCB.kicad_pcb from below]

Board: 2 copper layers, 231.3 x 182.5 mm, 99 parts (16 on the bottom side), 52 nets.

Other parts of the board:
SPK_L: Speaker_4R_3W_35x25mm
SPK_R: Speaker_4R_3W_35x25mm

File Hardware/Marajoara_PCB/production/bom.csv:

Designator,Footprint,Quantity,Value,LCSC Part #
BT1,SW_SPST_PTS647_Sx38,1,SW_Push,C455246
"C1, C34",CP_Elec_6.3x7.7,2,220uF,C25170691
"C10, C2",0805,2,10u,C15850
"C11, C12, C13, C14, C15, C16, C17, C18, C19, C20, C21, C22, C23, C24, C25, C26, C27, C28, C29, C3, C30, C31, C32, C33, C4, C5, C6, C7, C8, C9",0805,30,100nF,C49678
"D1, D10, D11, D12, D13, D14, D15, D16, D17, D18, D19, D2, D20, D21, D22, D23, D24, D25, D26, D27, D28, D3, D4, D5, D6, D7, D8, D9",WS2812B_PTH_staggered,28,WS2812B,
D29,D_SMA,1,SS14,C2480
D30,0805,1,LED_BLUE,C965817
D31,0805,1,LED_RED,C84256
"D32, D33",D_SOD-123,2,1N4148W,C83528
J1,TerminalBlock_Xinya_XY308-2.54-3P_1x03_P2.54mm_Horizontal,1,Conn_01x03_Socket,
PORT1,Hirose_DF13C_CL535-0404-8-51_1x04-1MP_P1.25mm_Vertical,1,Conn_01x04_Socket,C7433470
Q1,SOT-23_Handsoldering,1,XR5P04,C42456992
Q2,SOT-23,1,2N7002K,C65189
"R1, R11, R4",0805,3,330,C17630
"R10, R12, R13, R14, R15, R9",0805,6,100k,C149504
R16,0805,1,10k,C17414
"R2, R5, R6, R7, R8",0805,5,2.2k,C17520
R3,1206,1,220mR 1W 1%,C2683384
TOUCH1,PinHeader_1x03_P2.54mm_Vertical,1,Conn_01x03_Socket,
U1,ESOP-8_L4.9-W3.9-P1.27-LS6.0-BL-EP,1,TP4056,C382139
U2,ESP32-C3-Supermini,1,ESP32-C3-Supermini,
